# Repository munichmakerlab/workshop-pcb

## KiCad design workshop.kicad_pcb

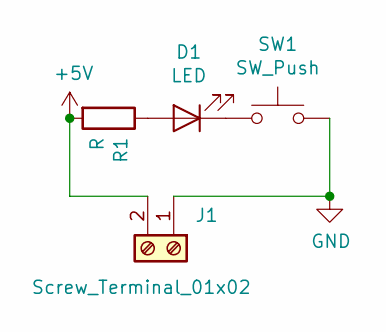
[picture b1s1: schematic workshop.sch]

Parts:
D1: LED; LED_D5.0mm
J1: Screw_Terminal_01x02; TerminalBlock_Phoenix_MKDS1.5-2pol
R1: R; R_Axial_DIN0309_L9.0mm_D3.2mm_P12.70mm_Horizontal
SW1: SW_Push; SW_PUSH_6mm

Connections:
+5V: J1.2, R1.2
GND: J1.1, SW1.2
unnamed: D1.1 (K), SW1.1
unnamed: D1.2 (A), R1.1

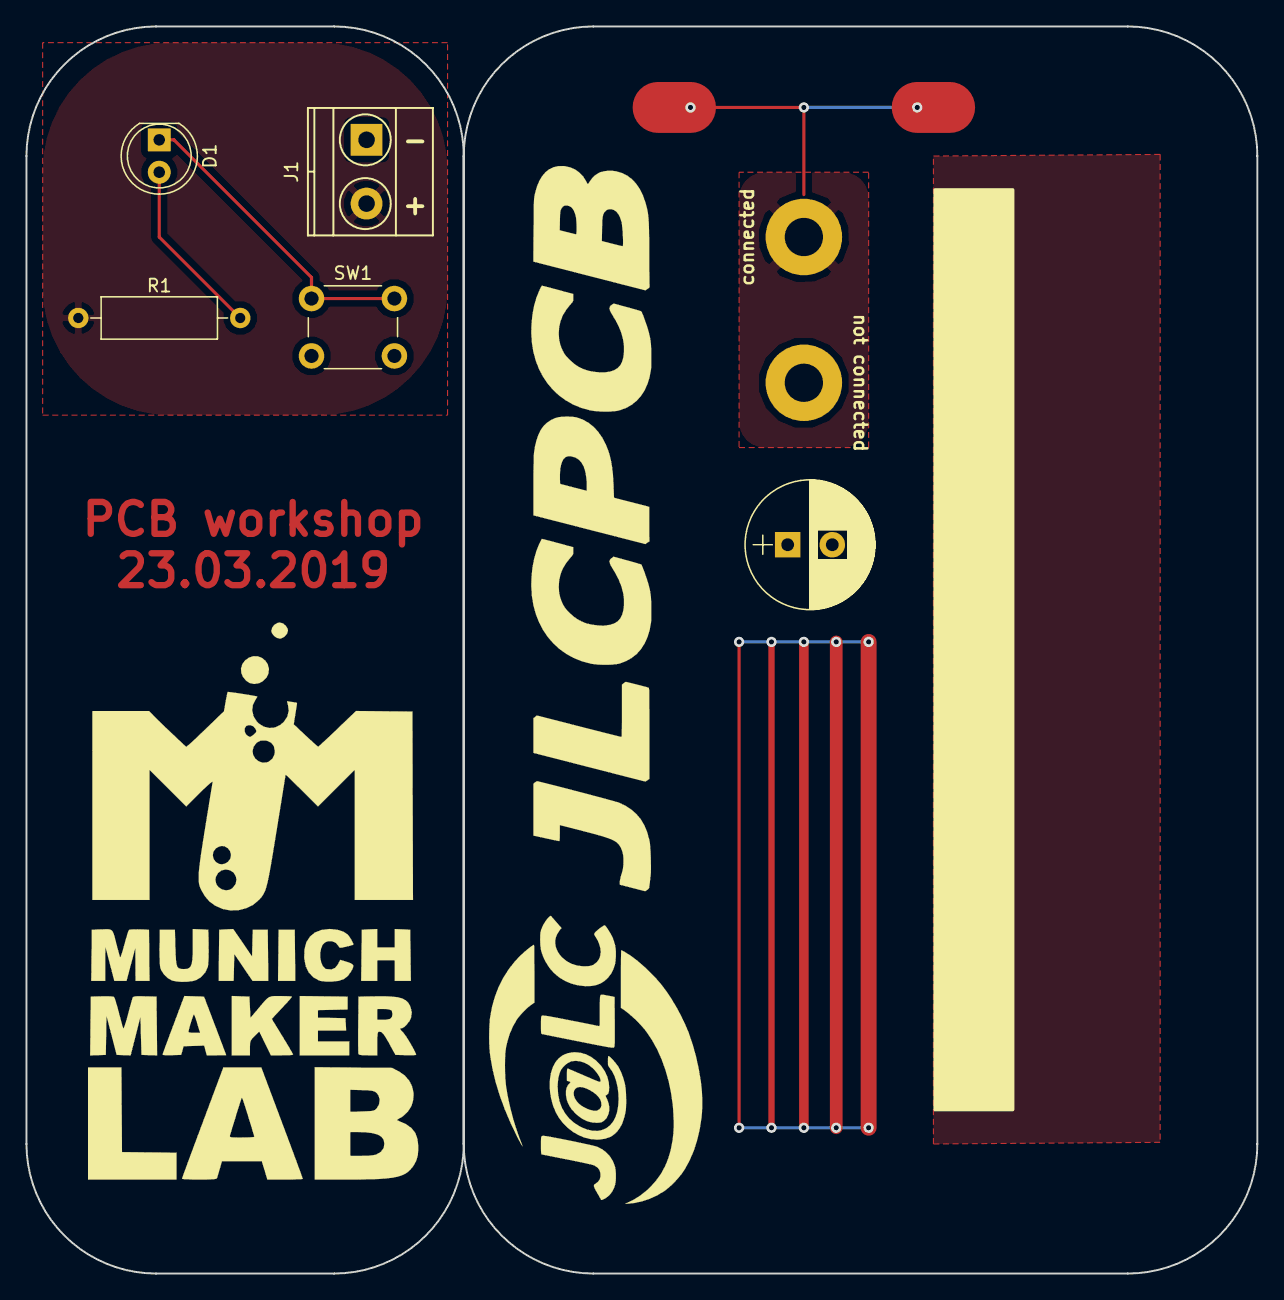
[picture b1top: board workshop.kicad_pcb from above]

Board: 2 copper layers, 96.5 x 97.8 mm, 4 parts (0 on the bottom side), 4 nets.
